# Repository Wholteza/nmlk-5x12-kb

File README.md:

# nmlk-5x12-kb

## Attributions

- Using kailh footprints from https://github.com/foostan/kbd

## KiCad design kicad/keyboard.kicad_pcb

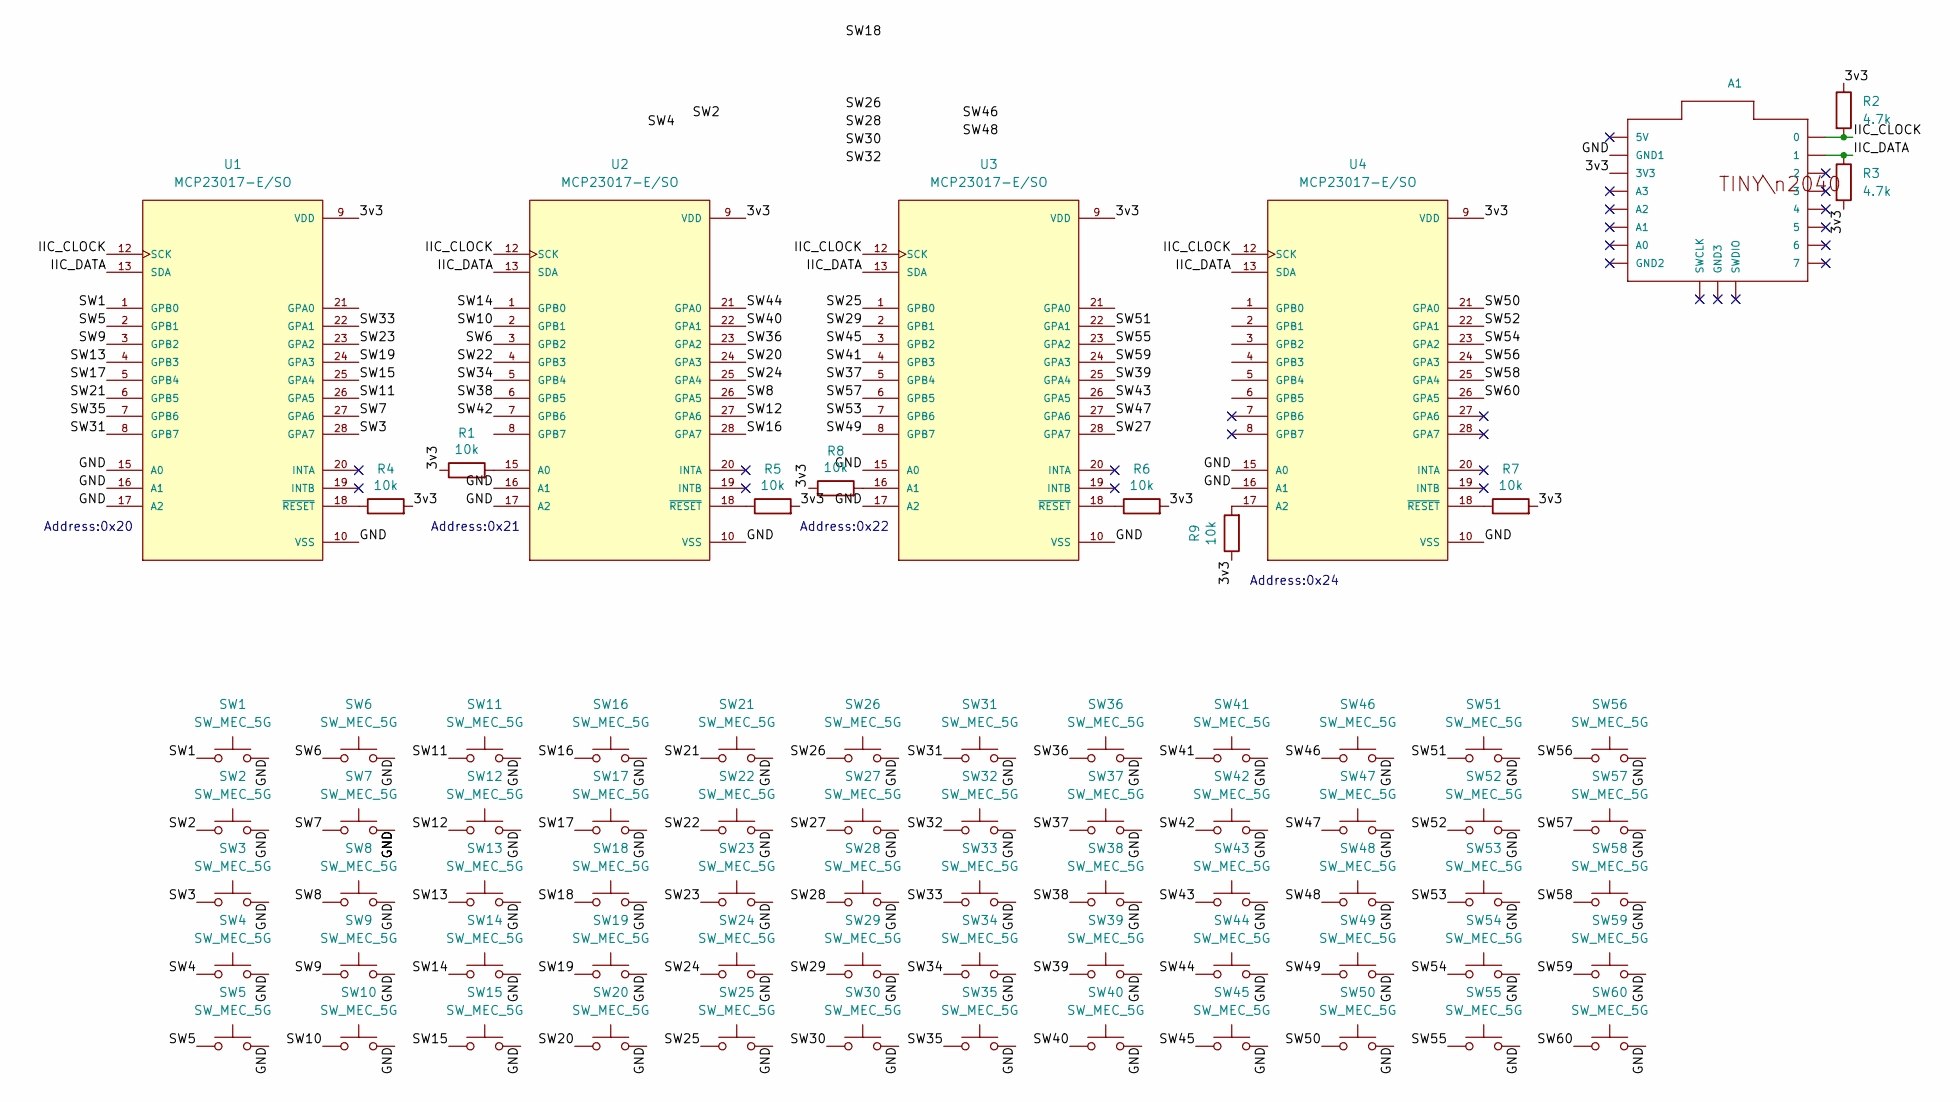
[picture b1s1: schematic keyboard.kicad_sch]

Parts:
A1: TINY2040-pimoroni-boards; pimoroni-boards-TINY2040
R1, R4, R5, R6, R7, R8, R9: 10k; R_0805_2012Metric_Pad1.20x1.40mm_HandSolder
R2, R3: 4.7k; R_0805_2012Metric_Pad1.20x1.40mm_HandSolder
SW1, SW2, SW3, SW4, SW5, SW6, SW7, SW8, SW9, SW10, SW11, SW12, SW13, SW14, SW15, SW16, SW17, SW18, SW19, SW20, SW21, SW22, SW23, SW24, SW25, SW26, SW27, SW28, SW29, SW30, SW31, SW32, SW33, SW34, SW35, SW36, SW37, SW38, SW39, SW40, SW41, SW42, SW43, SW44, SW45, SW46, SW47, SW48, SW49, SW50, SW51, SW52, SW53, SW54, SW55, SW56, SW57, SW58, SW59, SW60: SW_MEC_5G; CherryMX_ChocV2_1u
U1, U2, U3, U4: MCP23017-E/SO; SOIC127P1030X265-28N; PARTREV C

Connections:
/3v3: A1.3V3, R1.1, R2.1, R3.2, R4.2, R5.2, R6.2, R7.2, R8.1, R9.1, U1.9 (VDD), U2.9 (VDD), U3.9 (VDD), U4.9 (VDD)
/GND: A1.GND1, SW1.2 (B), SW2.2 (B), SW3.2 (B), SW4.2 (B), SW5.2 (B), SW6.2 (B), SW7.2 (B), SW8.2 (B), SW9.2 (B), SW10.2 (B), SW11.2 (B), SW12.2 (B), SW13.2 (B), SW14.2 (B), SW15.2 (B), SW16.2 (B), SW17.2 (B), SW18.2 (B), SW19.2 (B), SW20.2 (B), SW21.2 (B), SW22.2 (B), SW23.2 (B), SW24.2 (B), SW25.2 (B), SW26.2 (B), SW27.2 (B), SW28.2 (B), SW29.2 (B), SW30.2 (B), SW31.2 (B), SW32.2 (B), SW33.2 (B), SW34.2 (B), SW35.2 (B), SW36.2 (B), SW37.2 (B), SW38.2 (B), SW39.2 (B), SW40.2 (B), SW41.2 (B), SW42.2 (B), SW43.2 (B), SW44.2 (B), SW45.2 (B), SW46.2 (B), SW47.2 (B), SW48.2 (B), SW49.2 (B), SW50.2 (B), SW51.2 (B), SW52.2 (B), SW53.2 (B), SW54.2 (B), SW55.2 (B), SW56.2 (B), SW57.2 (B), SW58.2 (B), SW59.2 (B), SW60.2 (B), U1.10 (VSS), U1.15 (A0), U1.16 (A1), U1.17 (A2), U2.10 (VSS), U2.16 (A1), U2.17 (A2), U3.10 (VSS), U3.15 (A0), U3.17 (A2), U4.10 (VSS), U4.15 (A0), U4.16 (A1)
/IIC_CLOCK: A1.0, R2.2, U1.12 (SCK), U2.12 (SCK), U3.12 (SCK), U4.12 (SCK)
/IIC_DATA: A1.1, R3.1, U1.13 (SDA), U2.13 (SDA), U3.13 (SDA), U4.13 (SDA)
/SW1: SW1.1 (A), U1.1 (GPB0)
/SW2: SW2.1 (A)
/SW3: SW3.1 (A), U1.28 (GPA7)
/SW4: SW4.1 (A)
/SW5: SW5.1 (A), U1.2 (GPB1)
/SW6: SW6.1 (A), U2.3 (GPB2)
/SW7: SW7.1 (A), U1.27 (GPA6)
/SW8: SW8.1 (A), U2.26 (GPA5)
/SW9: SW9.1 (A), U1.3 (GPB2)
/SW10: SW10.1 (A), U2.2 (GPB1)
/SW11: SW11.1 (A), U1.26 (GPA5)
/SW12: SW12.1 (A), U2.27 (GPA6)
/SW13: SW13.1 (A), U1.4 (GPB3)
/SW14: SW14.1 (A), U2.1 (GPB0)
/SW15: SW15.1 (A), U1.25 (GPA4)
/SW16: SW16.1 (A), U2.28 (GPA7)
/SW17: SW17.1 (A), U1.5 (GPB4)
/SW18: SW18.1 (A)
/SW19: SW19.1 (A), U1.24 (GPA3)
/SW20: SW20.1 (A), U2.24 (GPA3)
/SW21: SW21.1 (A), U1.6 (GPB5)
/SW22: SW22.1 (A), U2.4 (GPB3)
/SW23: SW23.1 (A), U1.23 (GPA2)
/SW24: SW24.1 (A), U2.25 (GPA4)
/SW25: SW25.1 (A), U3.1 (GPB0)
/SW26: SW26.1 (A)
/SW27: SW27.1 (A), U3.28 (GPA7)
/SW28: SW28.1 (A)
/SW29: SW29.1 (A), U3.2 (GPB1)
/SW30: SW30.1 (A)
/SW31: SW31.1 (A), U1.8 (GPB7)
/SW32: SW32.1 (A)
/SW33: SW33.1 (A), U1.22 (GPA1)
/SW34: SW34.1 (A), U2.5 (GPB4)
/SW35: SW35.1 (A), U1.7 (GPB6)
/SW36: SW36.1 (A), U2.23 (GPA2)
/SW37: SW37.1 (A), U3.5 (GPB4)
/SW38: SW38.1 (A), U2.6 (GPB5)
/SW39: SW39.1 (A), U3.25 (GPA4)
/SW40: SW40.1 (A), U2.22 (GPA1)
/SW41: SW41.1 (A), U3.4 (GPB3)
/SW42: SW42.1 (A), U2.7 (GPB6)
/SW43: SW43.1 (A), U3.26 (GPA5)
/SW44: SW44.1 (A), U2.21 (GPA0)
/SW45: SW45.1 (A), U3.3 (GPB2)
/SW46: SW46.1 (A)
/SW47: SW47.1 (A), U3.27 (GPA6)
/SW48: SW48.1 (A)
/SW49: SW49.1 (A), U3.8 (GPB7)
/SW50: SW50.1 (A), U4.21 (GPA0)
/SW51: SW51.1 (A), U3.22 (GPA1)
/SW52: SW52.1 (A), U4.22 (GPA1)
/SW53: SW53.1 (A), U3.7 (GPB6)
/SW54: SW54.1 (A), U4.23 (GPA2)
/SW55: SW55.1 (A), U3.23 (GPA2)
/SW56: SW56.1 (A), U4.24 (GPA3)
/SW57: SW57.1 (A), U3.6 (GPB5)
/SW58: SW58.1 (A), U4.25 (GPA4)
/SW59: SW59.1 (A), U3.24 (GPA3)
/SW60: SW60.1 (A), U4.26 (GPA5)
unnamed: R1.2, U2.15 (A0)
unnamed: R4.1, U1.18 (~RESET)
unnamed: R5.1, U2.18 (~RESET)
unnamed: R6.1, U3.18 (~RESET)
unnamed: R7.1, U4.18 (~RESET)
unnamed: R8.2, U3.16 (A1)
unnamed: R9.2, U4.17 (A2)

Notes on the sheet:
Address:0x20
Address:0x22
Address:0x24
Address:0x21

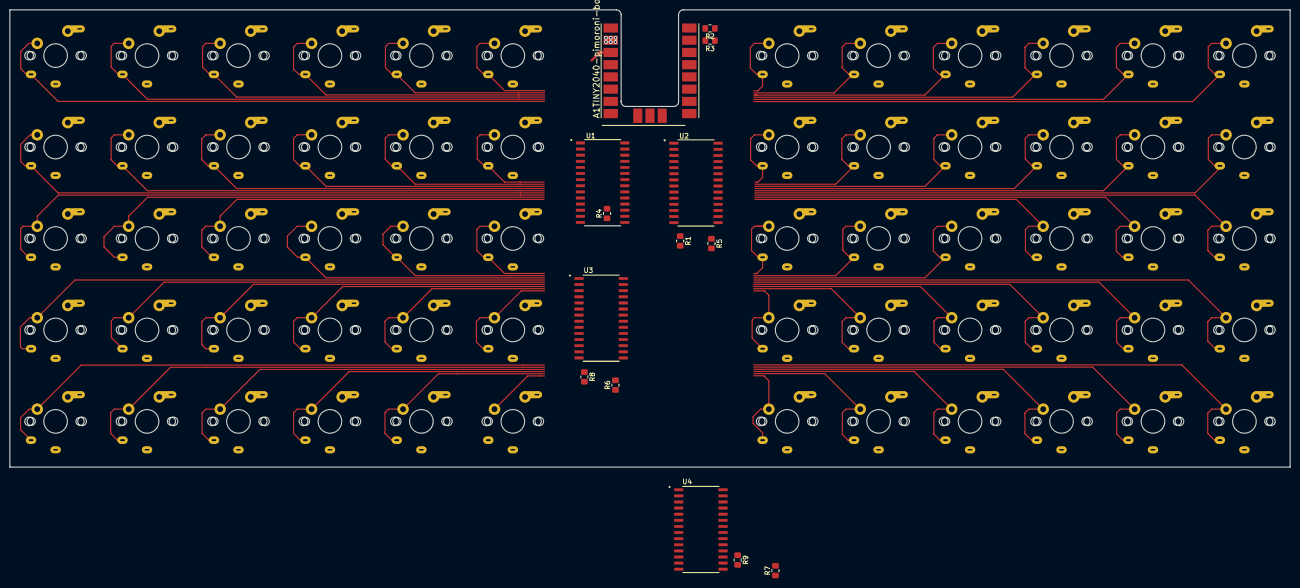
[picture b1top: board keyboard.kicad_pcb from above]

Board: 2 copper layers, 266.0 x 95.0 mm, 74 parts (0 on the bottom side), 62 nets.

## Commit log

2023-03-29 init
2023-03-29 Added kicad project
2023-04-01 Started on layout
2023-04-02 Started tracing signals, added jlcpcb settings
2023-04-06 wip tracing
2023-04-10 Reordered switch pins and re-traced
